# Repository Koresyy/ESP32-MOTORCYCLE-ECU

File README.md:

# ESP32-MOTORCYCLE-ECU (HARDWARE ONLY)

📌 THIS BOARD IS INTENDED FOR PROTOTYPING PURPOSES ONLY.  
📌 NO SOFTWARE/CODE IS INCLUDED IN THIS REPOSITORY.  
📌 THIS PROJECT FOCUSES EXCLUSIVELY ON THE HARDWARE DESIGN OF A MOTORCYCLE FUEL CONTROL SYSTEM USING ESP32.

## ⚙️ Overview

This project presents a **custom-designed PCB and schematic** for a fuel injection controller using the ESP32 microcontroller. It is suitable for small-displacement motorcycles and is designed with expandability in mind.

### Key Highlights
- Designed to handle RPM, MAP, IAT, TPS sensor inputs
- Injector driver circuit (compatible with Mio J injector)
- Power supply filtering and protection
- UART/I2C communication interface between controllers
- Expansion pins for future modules (e.g., speedometer, data logger)

## 🔒 Disclaimer

🚨 **THIS IS NOT A PRODUCTION-READY ECU.**  
This board is for **educational and prototyping use only**. Use with caution.  
Author is not responsible for any damage caused by misuse or improper wiring.

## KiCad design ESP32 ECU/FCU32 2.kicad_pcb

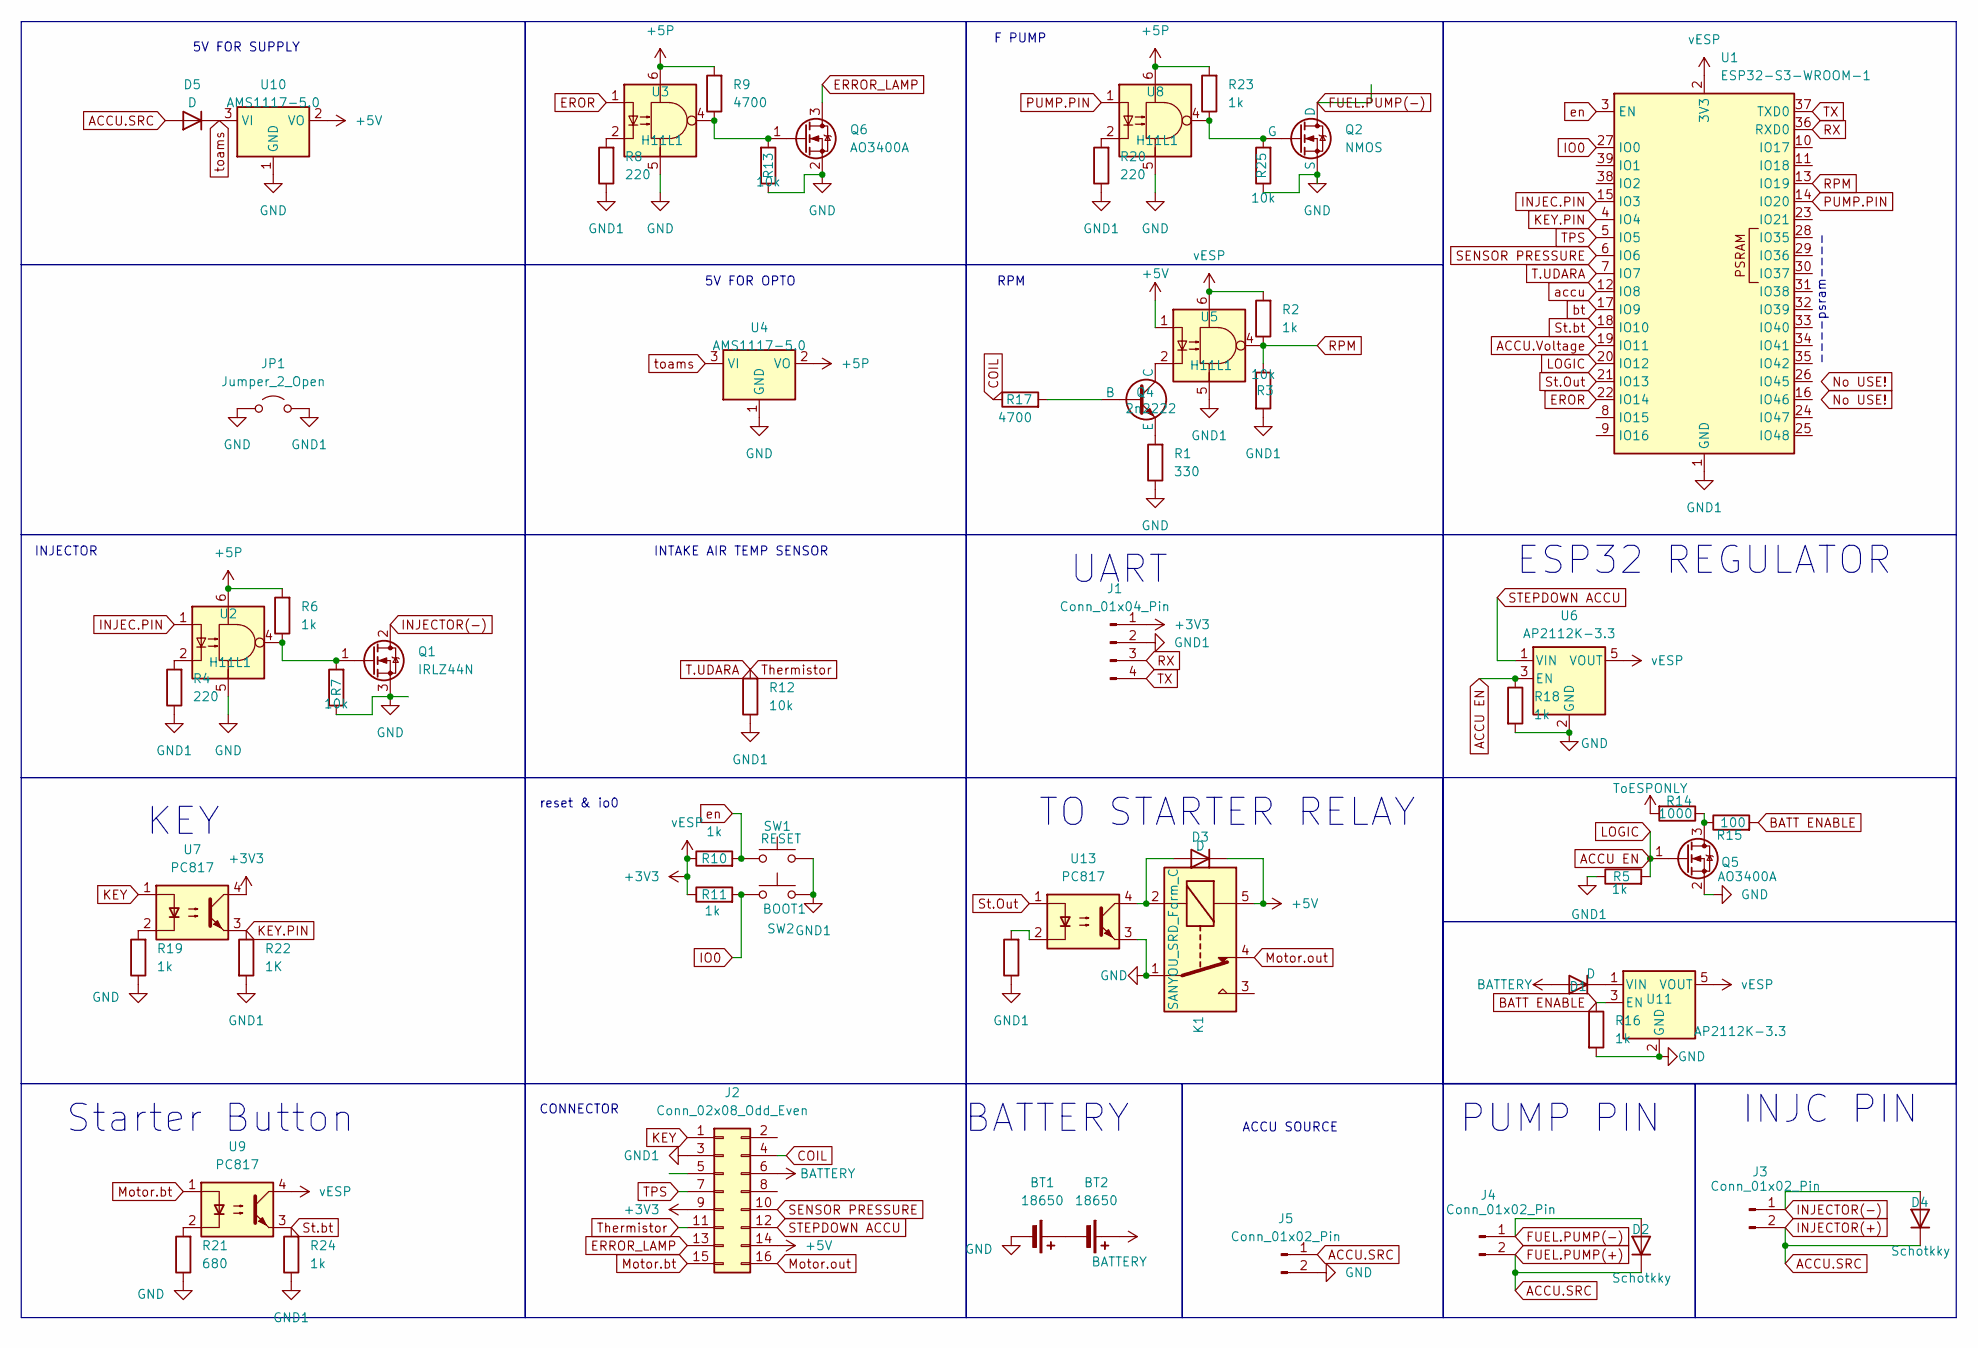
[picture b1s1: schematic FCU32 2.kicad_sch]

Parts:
BT1, BT2: 18650
D1, D3, D5: D; D_SMA
D2, D4: Schotkky; D_SMA
J1: Conn_01x04_Pin; PinHeader_1x04_P2.54mm_Horizontal
J2: Conn_02x08_Odd_Even; PinHeader_2x08_P2.54mm_Horizontal
J3, J4, J5: Conn_01x02_Pin; AMASS_XT30PW-M_1x02_P2.50mm_Horizontal
JP1: Jumper_2_Open; PinHeader_1x02_P2.54mm_Vertical
K1: SANYOU_SRD_Form_C; Relay_SPDT_SANYOU_SRD_Series_Form_C
Q1: IRLZ44N; TO-220-3_Vertical
Q2: NMOS; TO-252-2
Q4: 2n2222; SOT-23
Q5, Q6: AO3400A; SOT-23
R1: 330; R_1206_3216Metric_Pad1.30x1.75mm_HandSolder
R2, R5, R6, R10, R11, R16, R18, R19, R23, R24: 1k; R_1206_3216Metric_Pad1.30x1.75mm_HandSolder
R3, R7, R12, R13, R25: 10k; R_1206_3216Metric_Pad1.30x1.75mm_HandSolder
R4, R8, R20, R26: 220; R_1206_3216Metric_Pad1.30x1.75mm_HandSolder
R9, R17: 4700; R_1206_3216Metric_Pad1.30x1.75mm_HandSolder
R14: 1000; R_1206_3216Metric_Pad1.30x1.75mm_HandSolder
R15: 100; R_1206_3216Metric_Pad1.30x1.75mm_HandSolder
R21: 680; R_1206_3216Metric_Pad1.30x1.75mm_HandSolder
R22: 1K; R_1206_3216Metric_Pad1.30x1.75mm_HandSolder
SW1: RESET; SW_PUSH_6mm_H4.3mm
SW2: BOOT1; SW_PUSH_6mm_H4.3mm
U1: ESP32-S3-WROOM-1
U2, U3, U5, U8: H11L1; DIP-6_W7.62mm
U4, U10: AMS1117-5.0; SOT-223-3_TabPin2
U6, U11: AP2112K-3.3; SOT-23-5
U7, U9, U13: PC817; DIP-4_W7.62mm

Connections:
+3V3: J1.1, J2.9, R2.2, R10.1, R11.1, U1.2 (3V3), U5.6, U6.5 (VOUT), U7.4, U9.4, U11.5 (VOUT)
+5P: R6.2, R9.2, R23.2, U2.6, U3.6, U4.2 (VO), U8.6
+5V: D3.1 (K), J2.14, K1.5, U5.1, U10.2 (VO)
ACCU EN: Q5.1 (G), R5.2, R18.1, U1.20 (IO12), U6.3 (EN)
ACCU.SRC: D2.1 (K), D4.1 (K), D5.2 (A), J3.2, J4.2, J5.1
ACCU.Voltage: U1.19 (IO11)
BATT ENABLE: R15.2, R16.1, U11.3 (EN)
BATTERY: BT2.1 (+), D1.2 (A), J2.6
COIL: J2.4, R17.1
EROR: U1.22 (IO14), U3.1
ERROR_LAMP: J2.13, Q6.3 (D)
FUEL.PUMP(-): D2.2 (A), J4.1, Q2.1 (D)
GND: BT1.2 (-), J5.2, JP1.1 (A), K1.1, Q1.3 (S), Q2.3 (S), Q5.2 (S), Q6.2 (S), R1.1, R7.1, R13.1, R16.2, R18.2, R19.1, R21.1, R25.1, U2.5, U3.5, U4.1 (GND), U6.2 (GND), U8.5, U10.1 (GND), U11.2 (GND), U13.3
GND1: J1.2, J2.3, JP1.2 (B), R3.2, R4.1, R5.1, R8.1, R12.1, R20.1, R22.2, R24.1, R26.1, SW1.2, SW2.2, U1.1 (GND), U1.40 (GND), U1.41 (GND), U5.5
INJEC.PIN: U1.15 (IO3), U2.1
INJECTOR(-): D4.2 (A), J3.1, Q1.2 (D)
IO0: R11.2, SW2.1, U1.27 (IO0)
KEY: J2.1, U7.1
KEY.PIN: R22.1, U1.4 (IO4), U7.3
Motor.bt: J2.15, U9.1
Motor.out: J2.16, K1.4
unnamed: BT1.1 (+), BT2.2 (-)
unnamed: D1.1 (K), U11.1 (VIN)
unnamed: D3.2 (A), K1.2, U13.4
unnamed: Q1.1 (G), R6.1, R7.2, U2.4
unnamed: Q2.2 (G), R23.1, R25.2, U8.4
unnamed: Q4.2 (B), R17.2
unnamed: Q4.1 (C), U5.2
unnamed: Q4.3 (E), R1.2
unnamed: Q5.3 (D), R14.1, R15.1
unnamed: Q6.1 (G), R9.1, R13.2, U3.4
unnamed: R4.2, U2.2
unnamed: R8.2, U3.2
unnamed: R19.2, U7.2
unnamed: R20.2, U8.2
unnamed: R21.2, U9.2
unnamed: R26.2, U13.2
PUMP.PIN: U1.14 (IO20), U8.1
RPM: R2.1, R3.1, U1.13 (IO19), U5.4
RX: J1.3, U1.36 (RXD0)
SENSOR PRESSURE: J2.10, U1.6 (IO6)
STEPDOWN ACCU: J2.12, U6.1 (VIN)
St.Out: U1.21 (IO13), U13.1
St.bt: R24.2, U1.18 (IO10), U9.3
T.UDARA: J2.11, R12.2, U1.7 (IO7)
TPS: J2.7, U1.5 (IO5)
TX: J1.4, U1.37 (TXD0)
ToESPONLY: R14.2
accu: U1.12 (IO8)
bt: U1.17 (IO9)
en: R10.2, SW1.1, U1.3 (EN)
toams: D5.1 (K), U4.3 (VI), U10.3 (VI)

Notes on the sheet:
ACCU SOURCE
reset & io0
Starter Button
ESP32 REGULATOR
----psram----
UART
TO STARTER RELAY
INJC PIN
5V FOR OPTO
F PUMP
5V FOR SUPPLY
INTAKE AIR TEMP SENSOR
PUMP PIN
CONNECTOR
BATTERY
INJECTOR
KEY
RPM

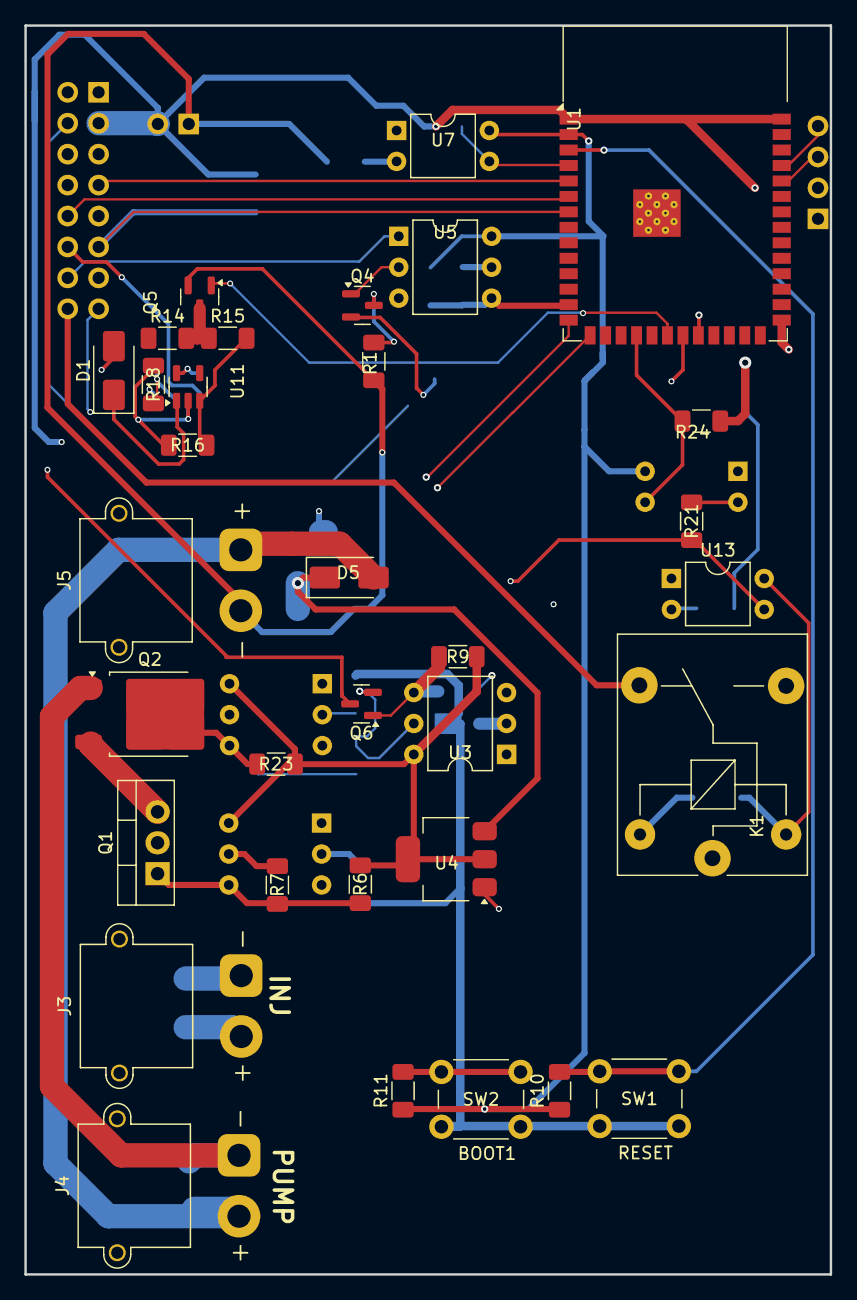
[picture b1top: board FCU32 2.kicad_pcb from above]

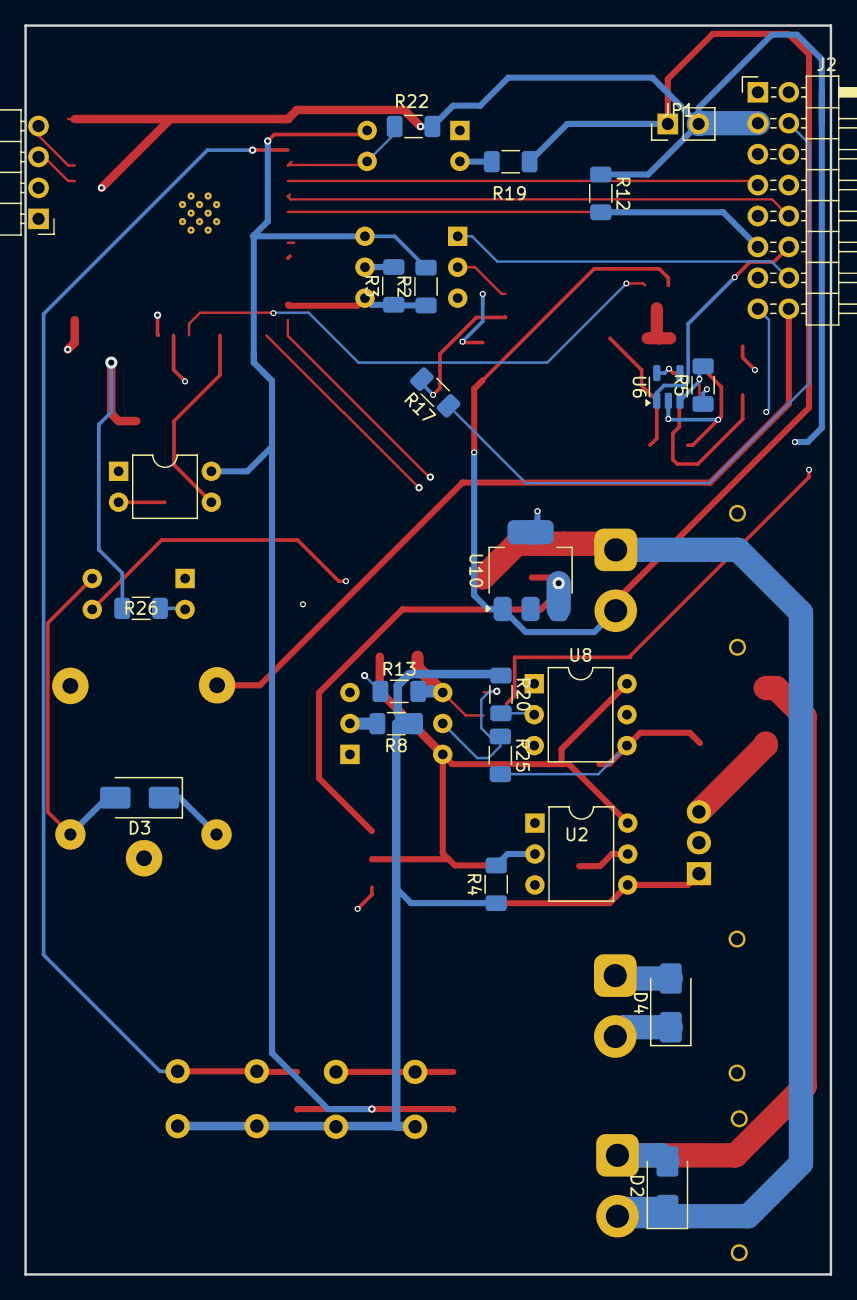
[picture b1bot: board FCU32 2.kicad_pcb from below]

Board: 4 copper layers, 66.1 x 102.6 mm, 57 parts (24 on the bottom side), 47 nets.

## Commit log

2025-05-01 README.md
